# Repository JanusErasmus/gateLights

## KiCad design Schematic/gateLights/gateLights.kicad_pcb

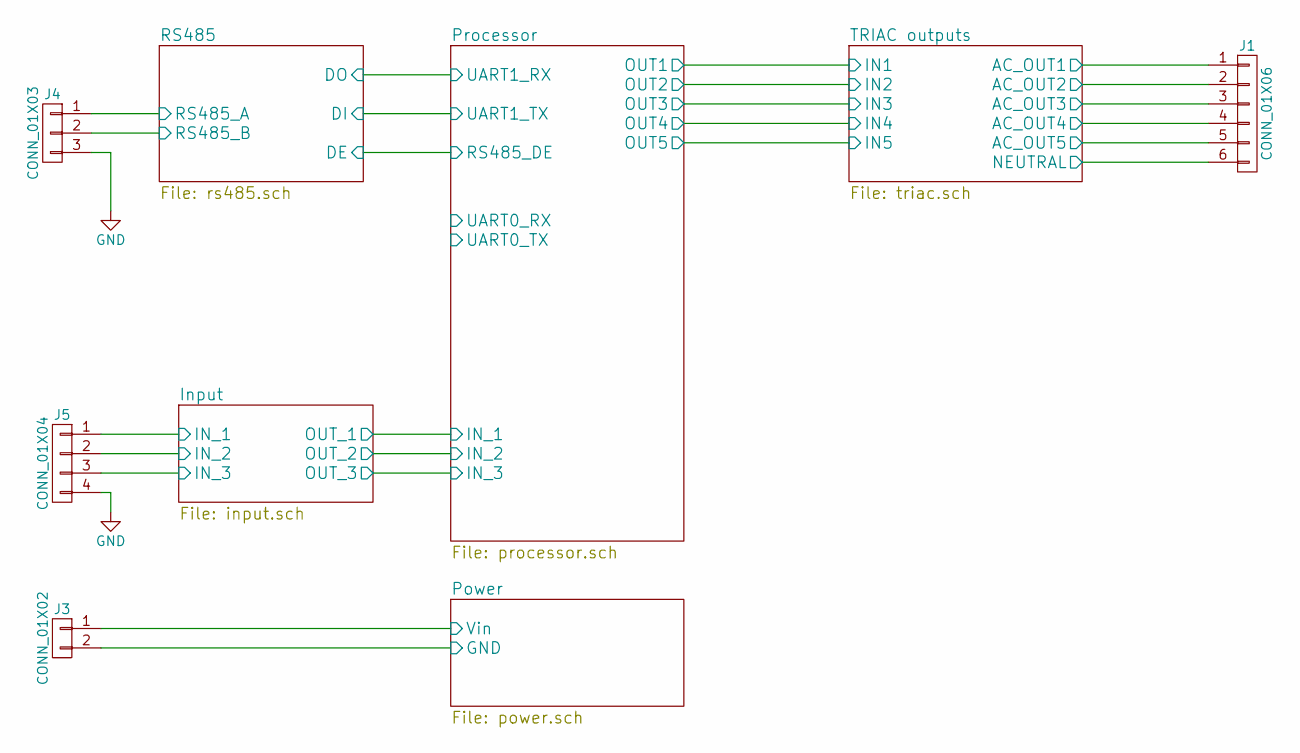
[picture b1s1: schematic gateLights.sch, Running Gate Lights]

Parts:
J1: CONN_01X06; Pin_Header_Straight_1x6_Pitch5.08mm
J3: CONN_01X02; Pin_Header_Straight_1x02_Pitch2.54mm
J4: CONN_01X03; Pin_Header_Straight_1x03_Pitch2.54mm
J5: CONN_01X04; Pin_Header_Straight_1x04_Pitch2.54mm

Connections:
/Input/IN_1: J5.1; also elsewhere on the board
/Input/IN_2: J5.2; also elsewhere on the board
/Input/IN_3: J5.3; also elsewhere on the board
/Power/Vin: J3.1; also elsewhere on the board
/RS485/RS485_A: J4.1; also elsewhere on the board
/RS485/RS485_B: J4.2; also elsewhere on the board
/TRIAC outputs/AC_OUT1: J1.1; also elsewhere on the board
/TRIAC outputs/AC_OUT2: J1.2; also elsewhere on the board
/TRIAC outputs/AC_OUT3: J1.3; also elsewhere on the board
/TRIAC outputs/AC_OUT4: J1.4; also elsewhere on the board
/TRIAC outputs/AC_OUT5: J1.5; also elsewhere on the board
/TRIAC outputs/NEUTRAL: J1.6; also elsewhere on the board
GND: J3.2, J4.3, J5.4; also elsewhere on the board

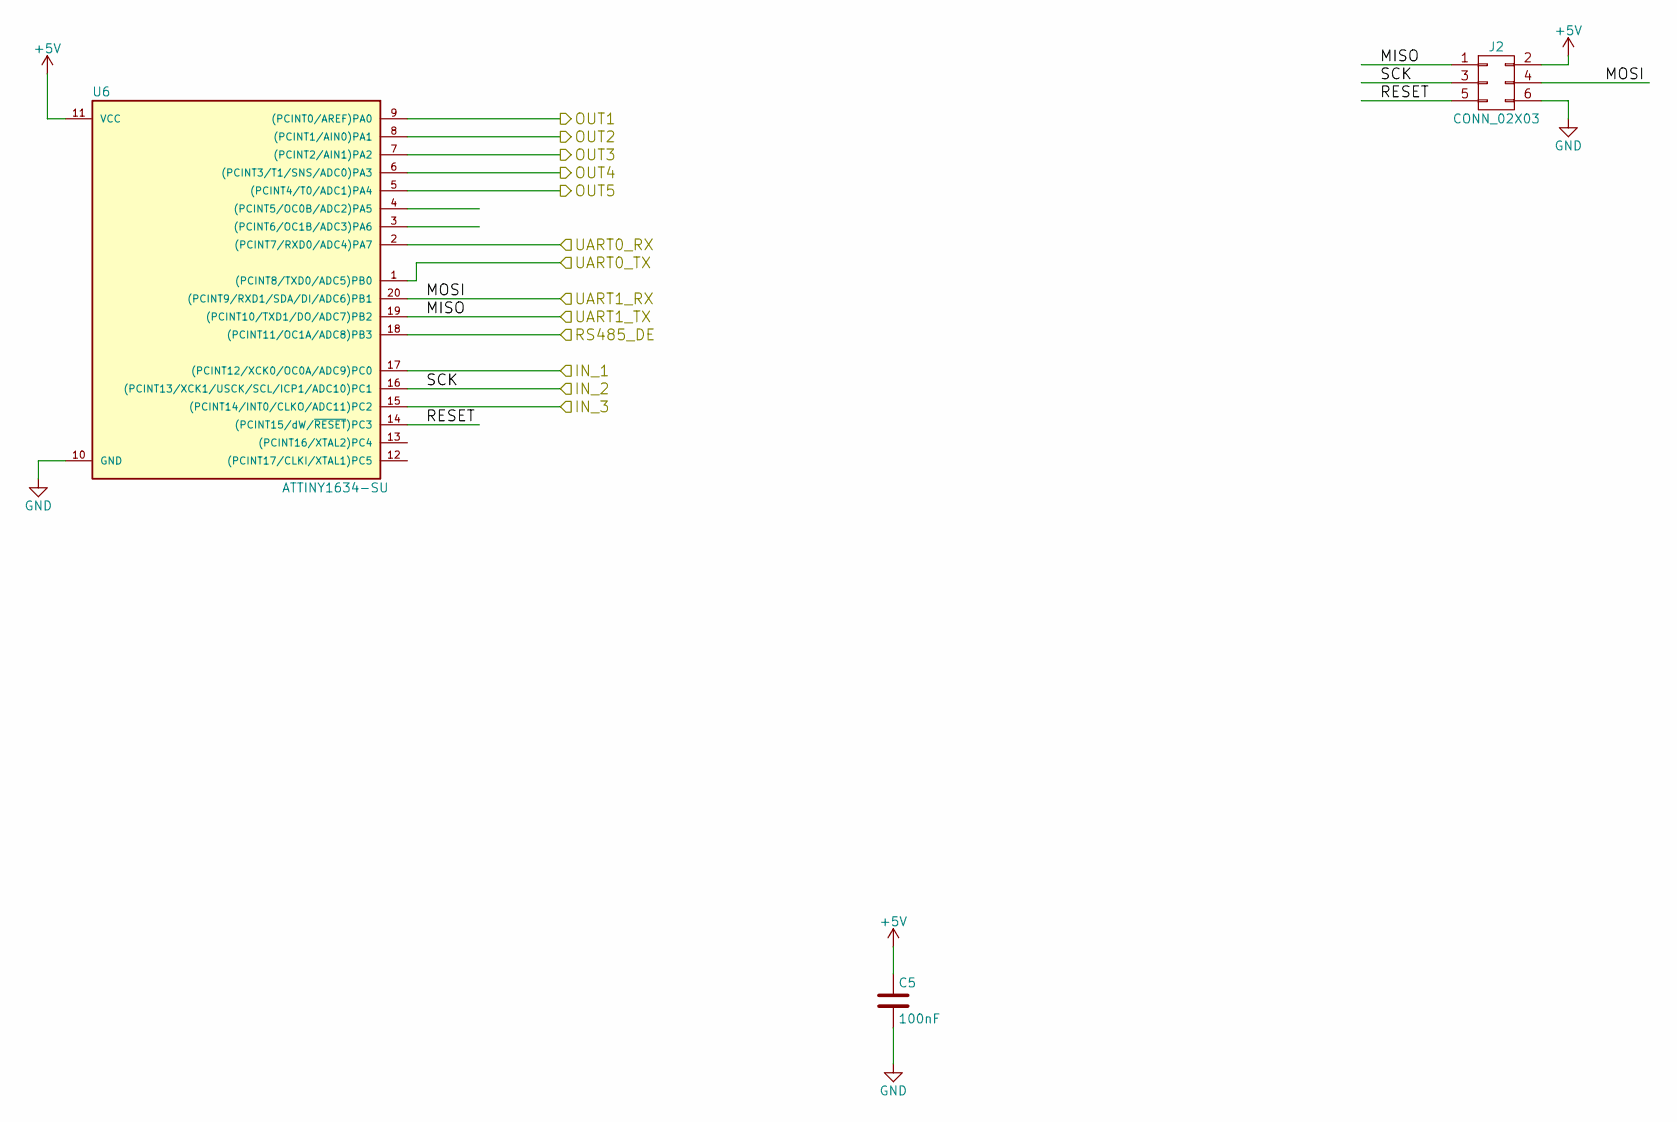
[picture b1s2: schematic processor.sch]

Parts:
C5: 100nF; C_0603_HandSoldering
J2: CONN_02X03; Pin_Header_Straight_2x03_Pitch2.54mm
U6: ATTINY1634-SU; SOIC-20W_7.5x12.8mm_Pitch1.27mm

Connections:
+5V: C5.1, J2.2, U6.11 (VCC); also elsewhere on the board
/Processor/IN_1: U6.17 ((PCINT12/XCK0/OC0A/ADC9)PC0); also elsewhere on the board
/Processor/IN_2: J2.3, U6.16 ((PCINT13/XCK1/USCK/SCL/ICP1/ADC10)PC1); also elsewhere on the board
/Processor/IN_3: U6.15 ((PCINT14/INT0/CLKO/ADC11)PC2); also elsewhere on the board
/Processor/RESET: J2.5, U6.14 ((PCINT15/dW/~RESET~)PC3)
/Processor/UART0_RX: U6.2 ((PCINT7/RXD0/ADC4)PA7)
/Processor/UART0_TX: U6.1 ((PCINT8/TXD0/ADC5)PB0)
/RS485/DE: U6.18 ((PCINT11/OC1A/ADC8)PB3); also elsewhere on the board
/RS485/DI: J2.1, U6.19 ((PCINT10/TXD1/DO/ADC7)PB2); also elsewhere on the board
/RS485/DO: J2.4, U6.20 ((PCINT9/RXD1/SDA/DI/ADC6)PB1); also elsewhere on the board
/TRIAC outputs/IN1: U6.9 ((PCINT0/AREF)PA0); also elsewhere on the board
/TRIAC outputs/IN2: U6.8 ((PCINT1/AIN0)PA1); also elsewhere on the board
/TRIAC outputs/IN3: U6.7 ((PCINT2/AIN1)PA2); also elsewhere on the board
/TRIAC outputs/IN4: U6.6 ((PCINT3/T1/SNS/ADC0)PA3); also elsewhere on the board
/TRIAC outputs/IN5: U6.5 ((PCINT4/T0/ADC1)PA4); also elsewhere on the board
GND: C5.2, J2.6, U6.10 (GND); also elsewhere on the board

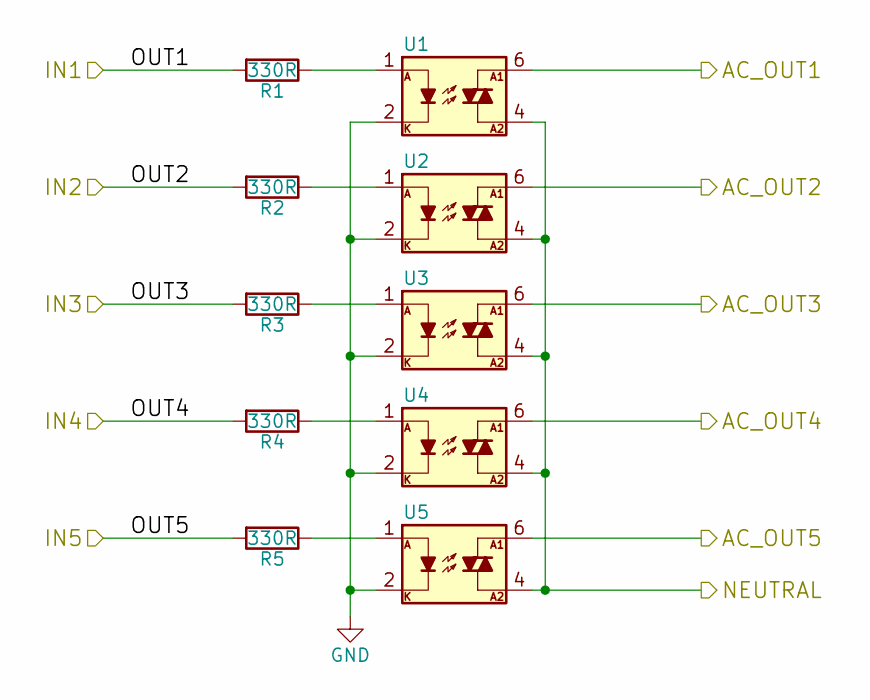
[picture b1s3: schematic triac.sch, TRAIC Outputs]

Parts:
R1, R2, R3, R4, R5: 330R; R_0603_HandSoldering
U1, U2, U3, U4, U5: OPTO-TRIAC MOC302x; DIP-6_W7.62mm

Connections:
/TRIAC outputs/AC_OUT1: U1.6; also elsewhere on the board
/TRIAC outputs/AC_OUT2: U2.6; also elsewhere on the board
/TRIAC outputs/AC_OUT3: U3.6; also elsewhere on the board
/TRIAC outputs/AC_OUT4: U4.6; also elsewhere on the board
/TRIAC outputs/AC_OUT5: U5.6; also elsewhere on the board
/TRIAC outputs/IN1: R1.2; also elsewhere on the board
/TRIAC outputs/IN2: R2.2; also elsewhere on the board
/TRIAC outputs/IN3: R3.2; also elsewhere on the board
/TRIAC outputs/IN4: R4.2; also elsewhere on the board
/TRIAC outputs/IN5: R5.2; also elsewhere on the board
/TRIAC outputs/NEUTRAL: U1.4, U2.4, U3.4, U4.4, U5.4; also elsewhere on the board
GND: U1.2, U2.2, U3.2, U4.2, U5.2; also elsewhere on the board
unnamed: R1.1, U1.1
unnamed: R2.1, U2.1
unnamed: R3.1, U3.1
unnamed: R4.1, U4.1
unnamed: R5.1, U5.1

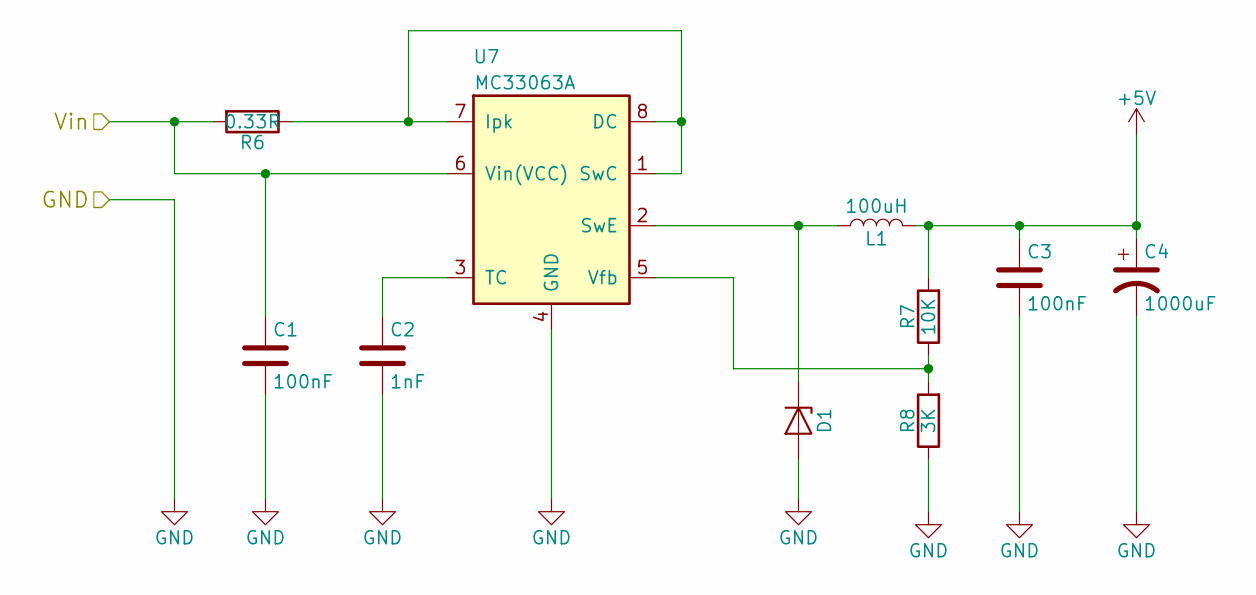
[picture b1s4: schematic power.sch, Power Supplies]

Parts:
C1, C3: 100nF; C_0603_HandSoldering
C2: 1nF; C_0603_HandSoldering
C4: 1000uF; CP_Elec_10x10
D1: SS16T3G; D_SMA_Handsoldering
L1: 100uH; SCD1005
R6: 0.33R; R_1206_HandSoldering
R7: 10K; R_0603_HandSoldering
R8: 3K; R_0603_HandSoldering
U7: MC33063A; SOIC-8_3.9x4.9mm_Pitch1.27mm

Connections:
+5V: C3.1, C4.1, L1.2, R7.2; also elsewhere on the board
/Power/Vin: C1.1, R6.2, U7.6 (Vin(VCC)); also elsewhere on the board
GND: C1.2, C2.2, C3.2, C4.2, D1.2 (A), R8.1, U7.4 (GND); also elsewhere on the board
unnamed: C2.1, U7.3 (TC)
unnamed: D1.1 (K), L1.1, U7.2 (SwE)
unnamed: R6.1, U7.1 (SwC), U7.7 (Ipk), U7.8 (DC)
unnamed: R7.1, R8.2, U7.5 (Vfb)

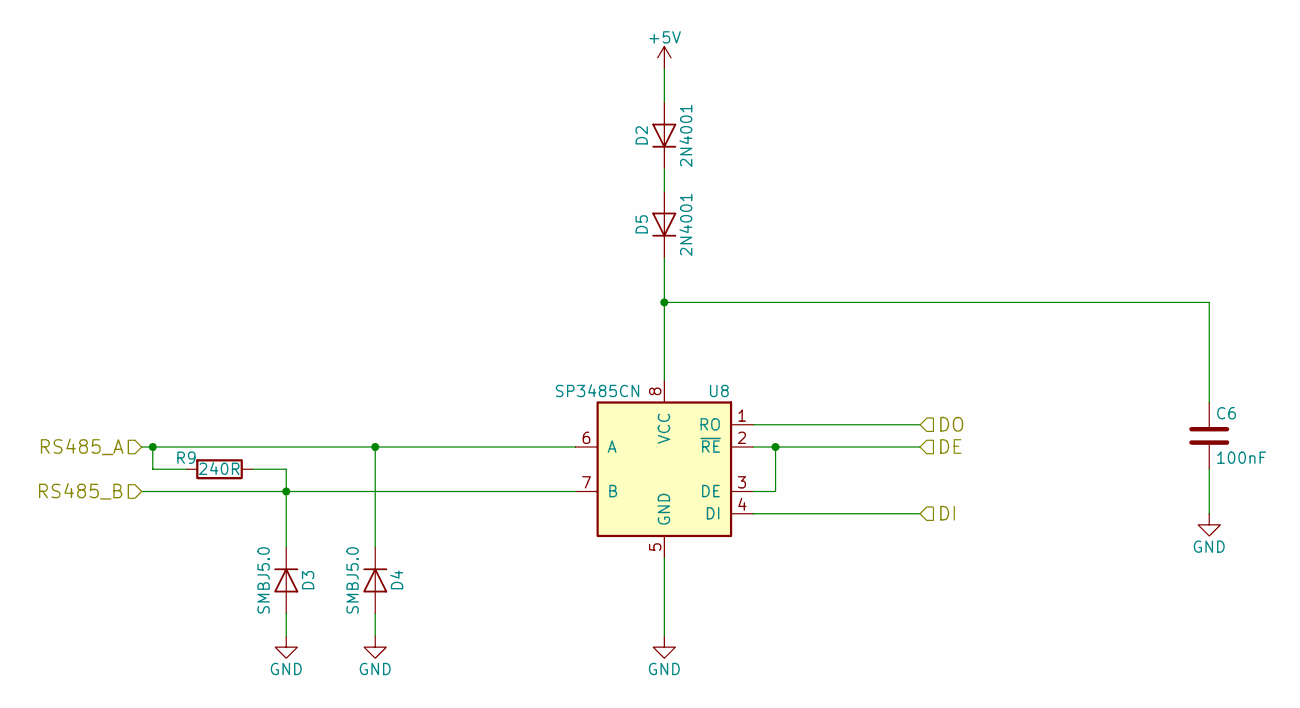
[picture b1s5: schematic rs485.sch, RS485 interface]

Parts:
C6: 100nF; C_0603_HandSoldering
D2, D5: 2N4001; D_DO-15_P12.70mm_Horizontal
D3, D4: SMBJ5.0; D_SMB_Handsoldering
R9: 240R; R_1206_HandSoldering
U8: SP3485CN; SOIC-8_3.9x4.9mm_Pitch1.27mm

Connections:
+5V: D2.2 (A); also elsewhere on the board
/RS485/DE: U8.2 (~RE~), U8.3 (DE); also elsewhere on the board
/RS485/DI: U8.4 (DI); also elsewhere on the board
/RS485/DO: U8.1 (RO); also elsewhere on the board
/RS485/RS485_A: D4.1 (K), R9.2, U8.6 (A); also elsewhere on the board
/RS485/RS485_B: D3.1 (K), R9.1, U8.7 (B); also elsewhere on the board
GND: C6.2, D3.2 (A), D4.2 (A), U8.5 (GND); also elsewhere on the board
unnamed: C6.1, D5.1 (K), U8.8 (VCC)
unnamed: D2.1 (K), D5.2 (A)

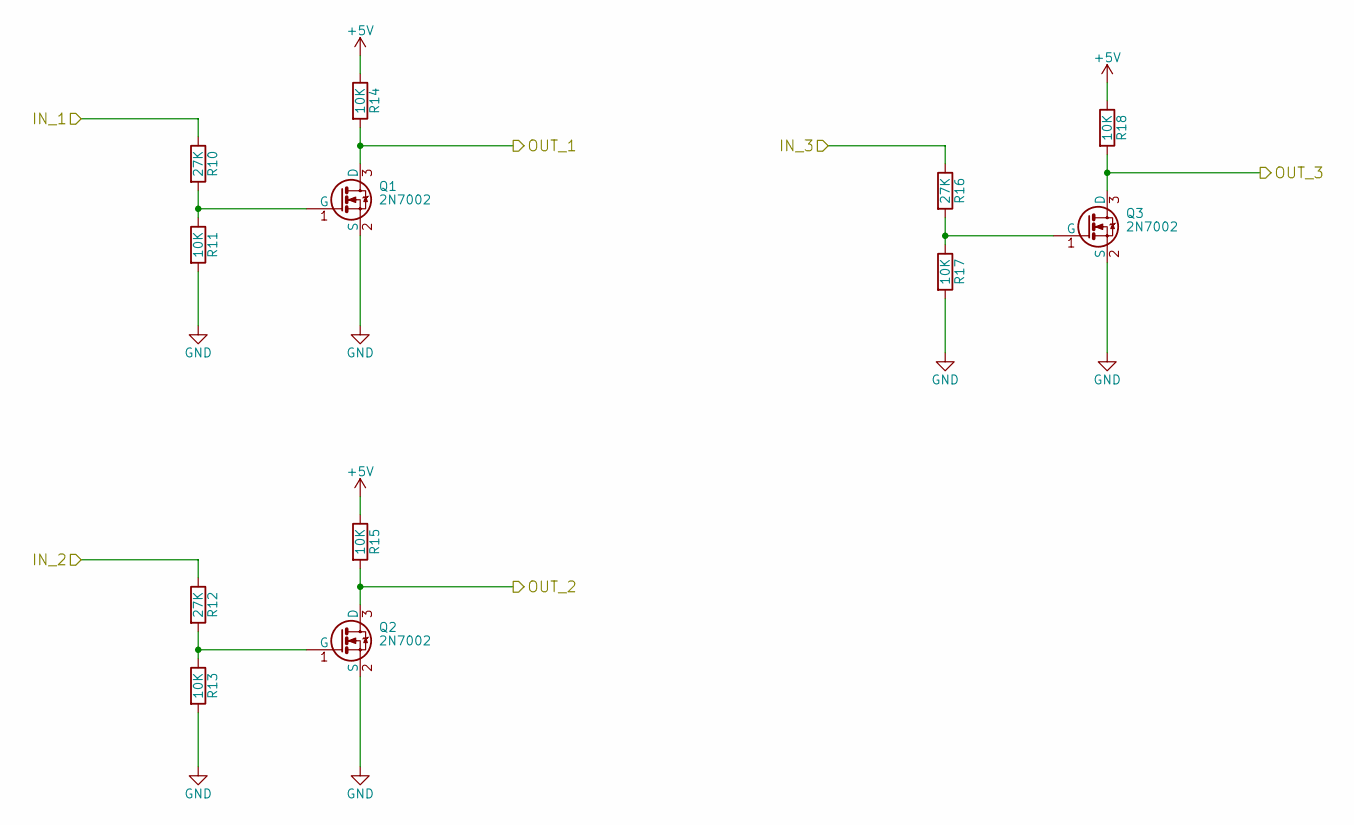
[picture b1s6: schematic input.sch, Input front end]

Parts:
Q1, Q2, Q3: 2N7002; SOT-23
R10, R12, R16: 27K; R_1206_HandSoldering
R11, R13, R17: 10K; R_1206_HandSoldering
R14, R15, R18: 10K; R_0603_HandSoldering

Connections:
+5V: R14.1, R15.1, R18.1; also elsewhere on the board
/Input/IN_1: R10.1; also elsewhere on the board
/Input/IN_2: R12.1; also elsewhere on the board
/Input/IN_3: R16.1; also elsewhere on the board
/Processor/IN_1: Q1.3 (D), R14.2; also elsewhere on the board
/Processor/IN_2: Q2.3 (D), R15.2; also elsewhere on the board
/Processor/IN_3: Q3.3 (D), R18.2; also elsewhere on the board
GND: Q1.2 (S), Q2.2 (S), Q3.2 (S), R11.2, R13.2, R17.2; also elsewhere on the board
unnamed: Q1.1 (G), R10.2, R11.1
unnamed: Q2.1 (G), R12.2, R13.1
unnamed: Q3.1 (G), R16.2, R17.1

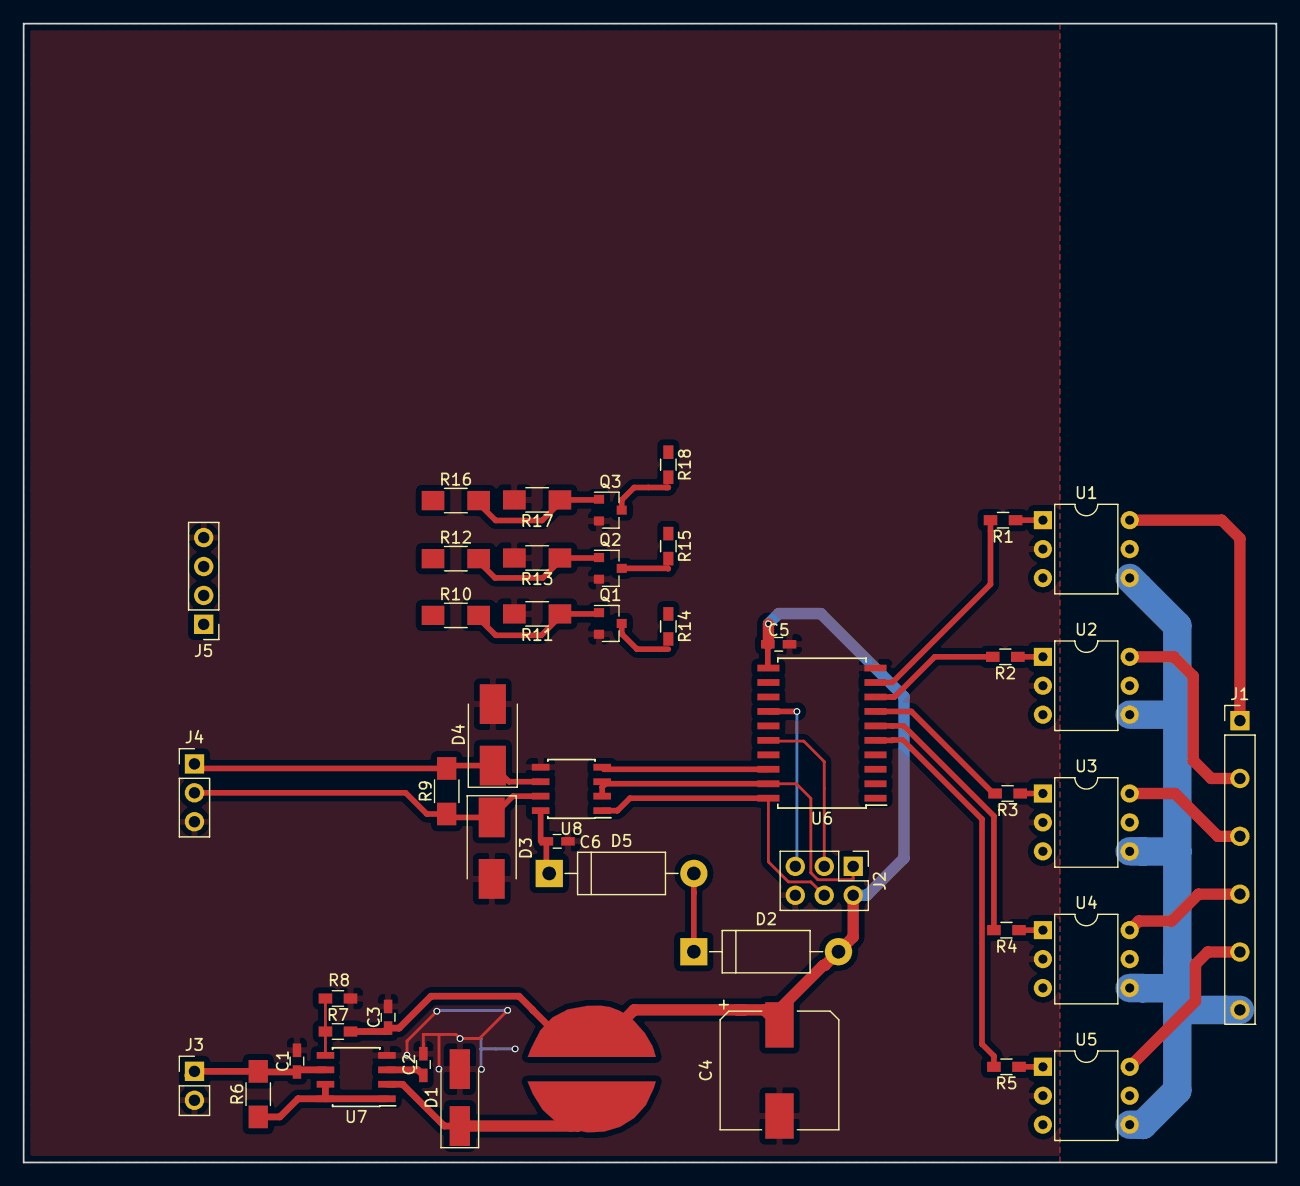
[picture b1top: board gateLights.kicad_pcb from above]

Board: 2 copper layers, 110.0 x 100.0 mm, 46 parts (0 on the bottom side), 40 nets.

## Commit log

2015-05-26 fixed some interrupt timings
2015-05-27 using a state machine to animate lights
2015-05-28 #1: Ligts run when inputs are toggling at 1 Hz, when on for longer than 2s, light are kept on, off light close off
2017-05-20 Add KiCAD design
2017-05-20 Add RS485
2017-05-23 RS485 protection
2017-06-06 Add inputs
2017-06-06 Fix resistor footprints
